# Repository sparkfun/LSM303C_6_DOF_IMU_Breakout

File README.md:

SparkFun LSM303C 6 DOF IMU Breakout
========================================

*[SparkFun LSM303C 6 DOF IMU Breakout (BOB-13303)](https://www.sparkfun.com/products/13303)*

The LSM303C is a triple axis accelerometer and triple axis magnetic sensor, providing 6D of orientation detection.

This part was created in Eagle v7.4.0

Repository Contents
-------------------

* **/Hardware** - All Eagle design files (.brd, .sch)
* **/Libraries** - All Arduino libraries and board examples
* **/Production** - Test bed files and production panel files

Documentation
--------------
* **[Arduino Library](https://github.com/sparkfun/SparkFun_LSM303C_6_DOF_IMU_Breakout_Arduino_Library)** - Arduino library for the LSM303C.
* **[Hookup Guide](https://learn.sparkfun.com/tutorials/lsm303c-6dof-hookup-guide)** - Basic hookup guide for the LSM303C.
* **[SparkFun Fritzing repo](https://github.com/sparkfun/Fritzing_Parts)** - Fritzing diagrams for SparkFun products.
* **[SparkFun 3D Model repo](https://github.com/sparkfun/3D_Models)** - 3D models of SparkFun products. 
* **[SparkFun Graphical Datasheets](https://github.com/sparkfun/Graphical_Datasheets)** -Graphical Datasheets for various SparkFun products

Product Versions
----------------
* [BOB-13303](https://www.sparkfun.com/products/13303)- LSM303C based 6 DOF IMU beakout board

Version History
---------------
* [v1.0_H1.0](https://github.com/sparkfun/LSM303C_6_DOF_IMU_Breakout/releases/tag/v1.0_H1.0) - Removing old libraries. Adding links to formal libs in readme.
* [v1.0](https://github.com/sparkfun/LSM303C_6_DOF_IMU_Breakout/releases/tag/v1.0) - First (hopefully ony) product release.  v10 is SFE code for version 1.0

License Information
-------------------

This product is _**open source**_! 

Please review the LICENSE.md file for license information. 

If you have any questions or concerns on licensing, please contact techsupport@sparkfun.com.

Distributed as-is; no warranty is given.

- Your friends at SparkFun.

_<COLLABORATION CREDIT>_

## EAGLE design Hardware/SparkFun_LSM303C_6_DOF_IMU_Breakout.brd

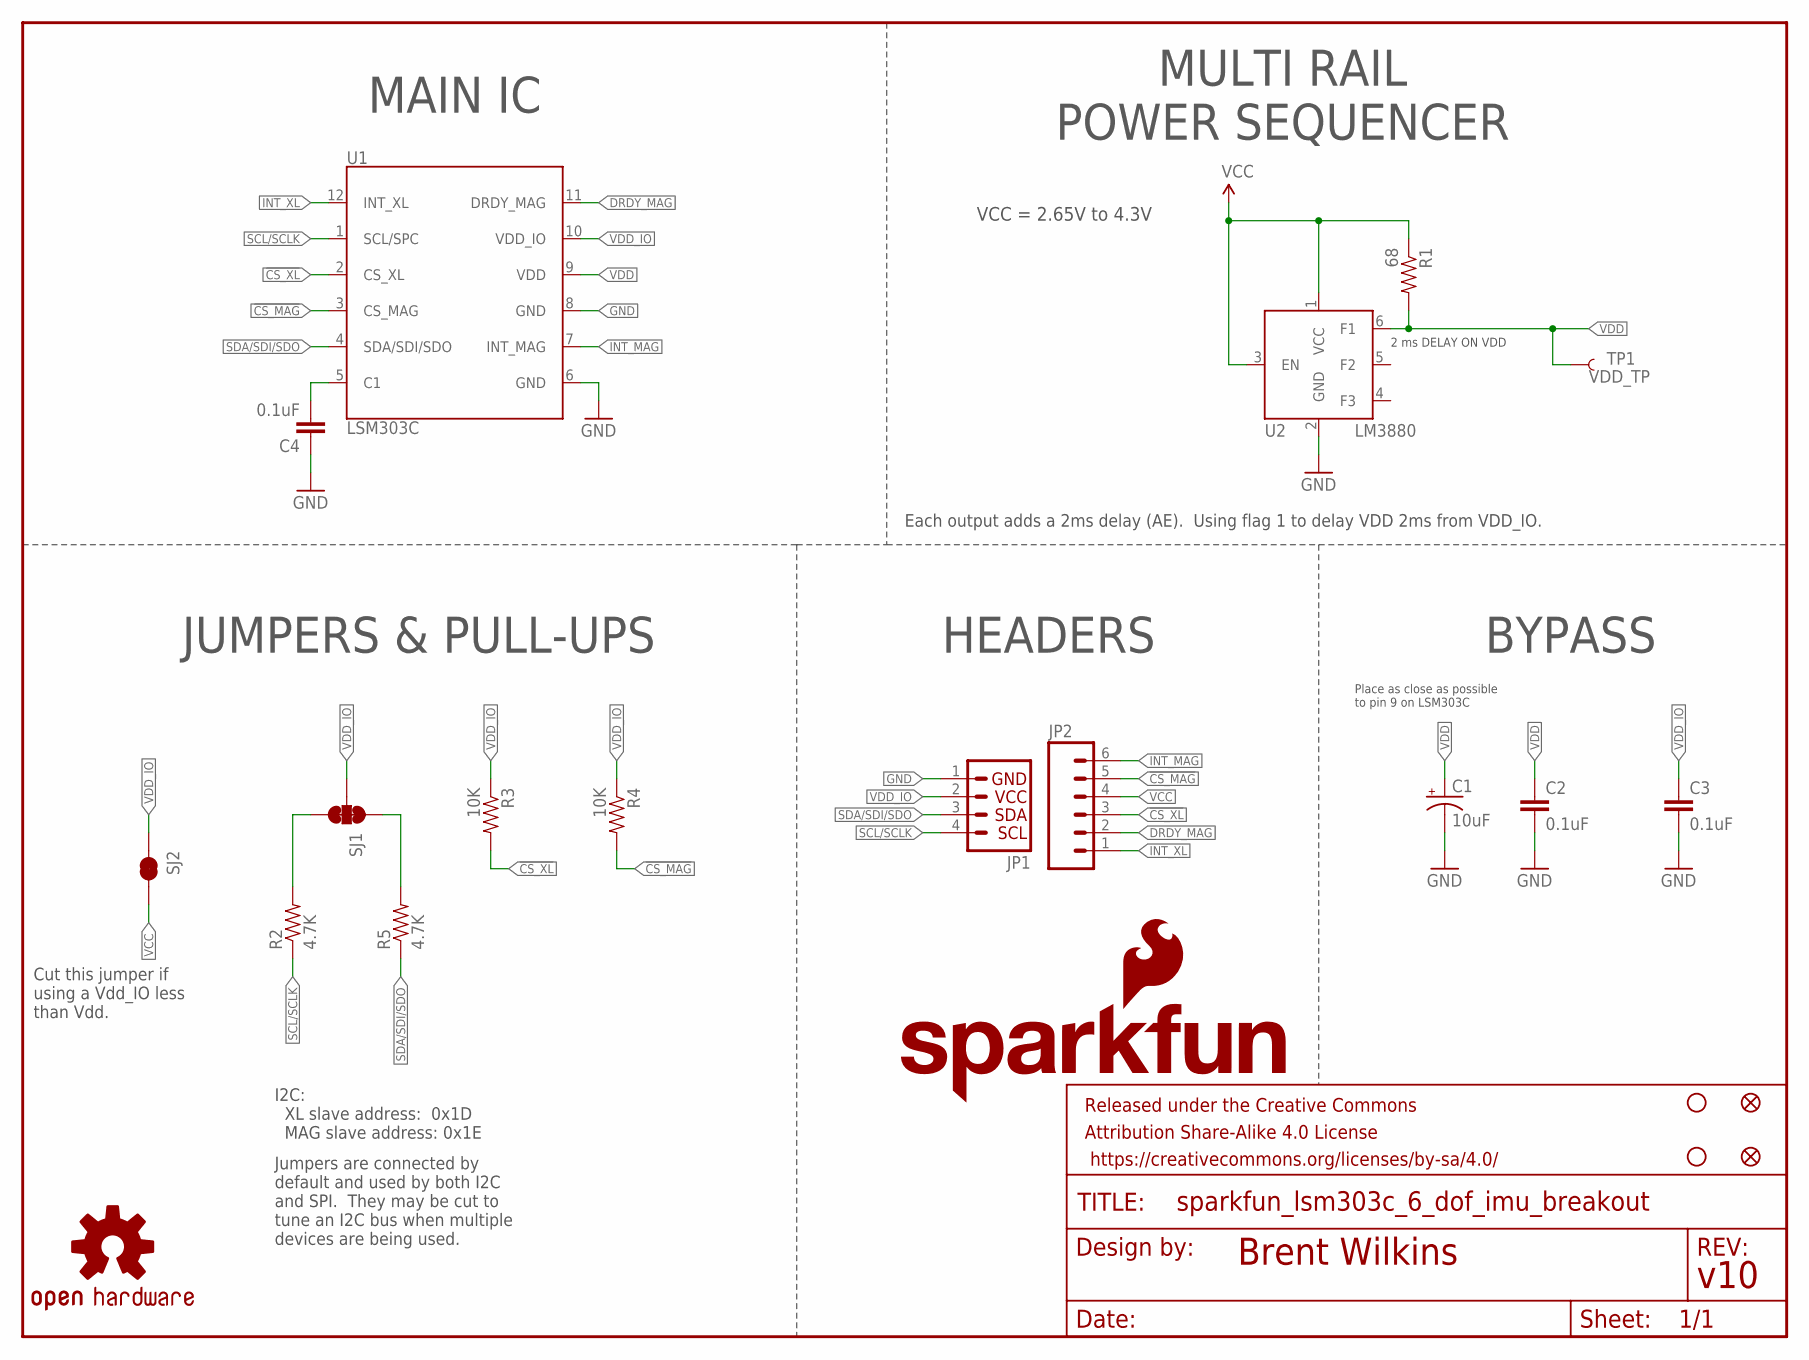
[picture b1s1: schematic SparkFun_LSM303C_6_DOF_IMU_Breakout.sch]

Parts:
C1: 10uF; EIA3216
C2, C3, C4: 0.1uF; 0603-CAP
FID1, FID2: FIDUCIAL1X2; FIDUCIAL-1X2
FRAME1: FRAME-LETTER; CREATIVE_COMMONS
JP1: I2C_STANDARD; 1X04
JP2: M06SILK_FEMALE_PTH; 1X06
LOGO1: SFE_LOGO_NAME.1_INCH; SFE_LOGO_NAME_.1
LOGO2: SFE_LOGO_FLAME.1EXP; SFE_LOGO_FLAME_COPPER_EXPOSED_.1
R1: 68; 0603-RES
R2, R5: 4.7K; 0603-RES
R3, R4: 10K; 0603-RES
SJ1: JUMPER-PAD-3-NC_BY_TRACE; PAD-JUMPER-3-3OF3_NC_BY_TRACE_YES_SILK_FULL_BOX
SJ2: JUMPER-PAD-2-NC_BY_TRACE; PAD-JUMPER-2-NC_BY_TRACE_YES_SILK
STANDOFF1, STANDOFF2: STAND-OFF
TP1: VDD_TP; TP_15TH
U1: LSM303C; LGA-12
U2: LM3880; SOT23-6
U$8: OSHW-LOGOS; OSHW-LOGO-S

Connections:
!CS_MAG: JP2.5, R4.2, U1.3 (CS_MAG)
!CS_XL: JP2.3, R3.2, U1.2 (CS_XL)
DRDY_MAG: JP2.2, U1.11 (DRDY_MAG)
GND: C1.C (-), C2.2, C3.2, C4.1, JP1.1, U1.6 (GND), U1.8 (GND), U2.2 (GND)
I2C-UP: R5.2, SJ1.1
INT_MAG: JP2.6, U1.7 (INT_MAG)
INT_XL: JP2.1, U1.12 (INT_XL)
unnamed: C4.2, U1.5 (C1)
unnamed: R2.2, SJ1.3
SCL/SCLK: JP1.4, R2.1, U1.1 (SCL/SPC)
SDA/SDI/SDO: JP1.3, R5.1, U1.4 (SDA/SDI/SDO)
VCC: JP2.4, R1.1, SJ2.2, U2.1 (VCC), U2.3 (EN)
VDD: C1.A (+), C2.1, R1.2, TP1.P$1, U1.9 (VDD), U2.6 (F1)
VDD_IO: C3.1, JP1.2, R3.1, R4.1, SJ1.2, SJ2.1, U1.10 (VDD_IO)

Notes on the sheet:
2 ms DELAY ON VDD
Place as close as possible to pin 9 on LSM303C
I2C: XL slave address: 0x1D MAG slave address: 0x1E
JUMPERS & PULL-UPS
HEADERS
BYPASS
MULTI RAIL POWER SEQUENCER
MAIN IC
Each output adds a 2ms delay (AE). Using flag 1 to delay VDD 2ms from VDD_IO.
Cut this jumper if using a Vdd_IO less than Vdd.
Jumpers are connected by default and used by both I2C and SPI. They may be cut to tune an I2C bus when multiple devices are being used.
VCC = 2.65V to 4.3V

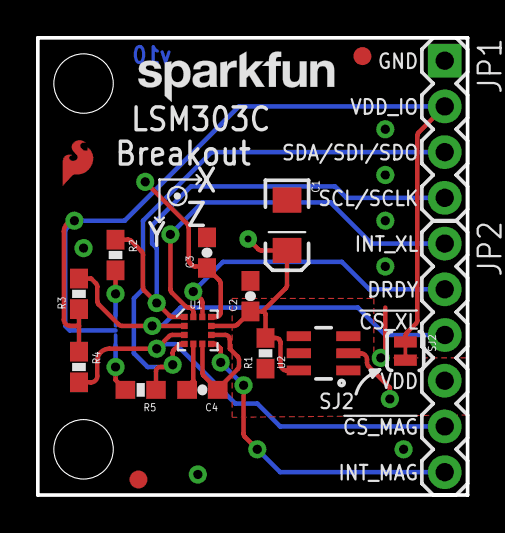
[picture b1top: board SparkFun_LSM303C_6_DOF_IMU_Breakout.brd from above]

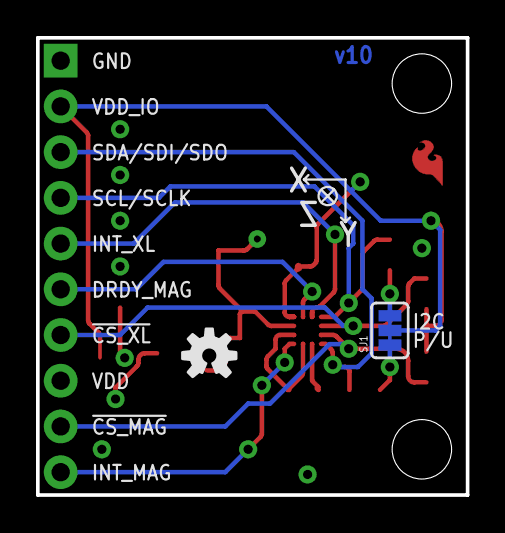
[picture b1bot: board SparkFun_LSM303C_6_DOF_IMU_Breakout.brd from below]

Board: 2 copper layers, 23.9 x 25.4 mm, 24 parts (2 on the bottom side), 14 nets.

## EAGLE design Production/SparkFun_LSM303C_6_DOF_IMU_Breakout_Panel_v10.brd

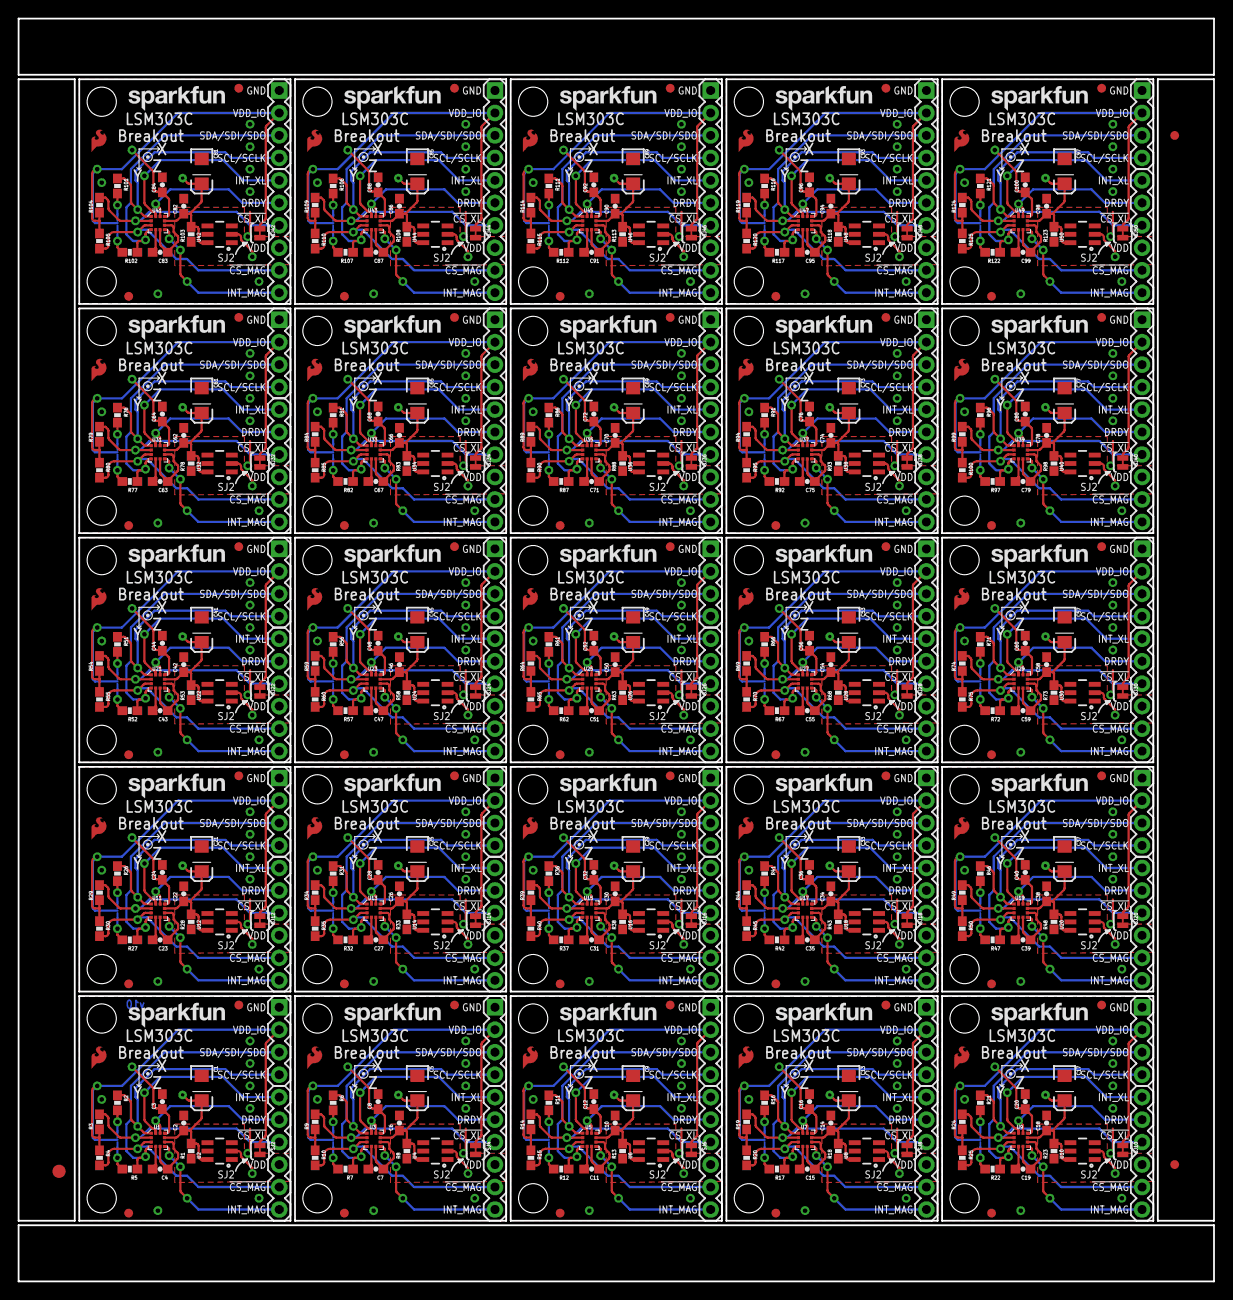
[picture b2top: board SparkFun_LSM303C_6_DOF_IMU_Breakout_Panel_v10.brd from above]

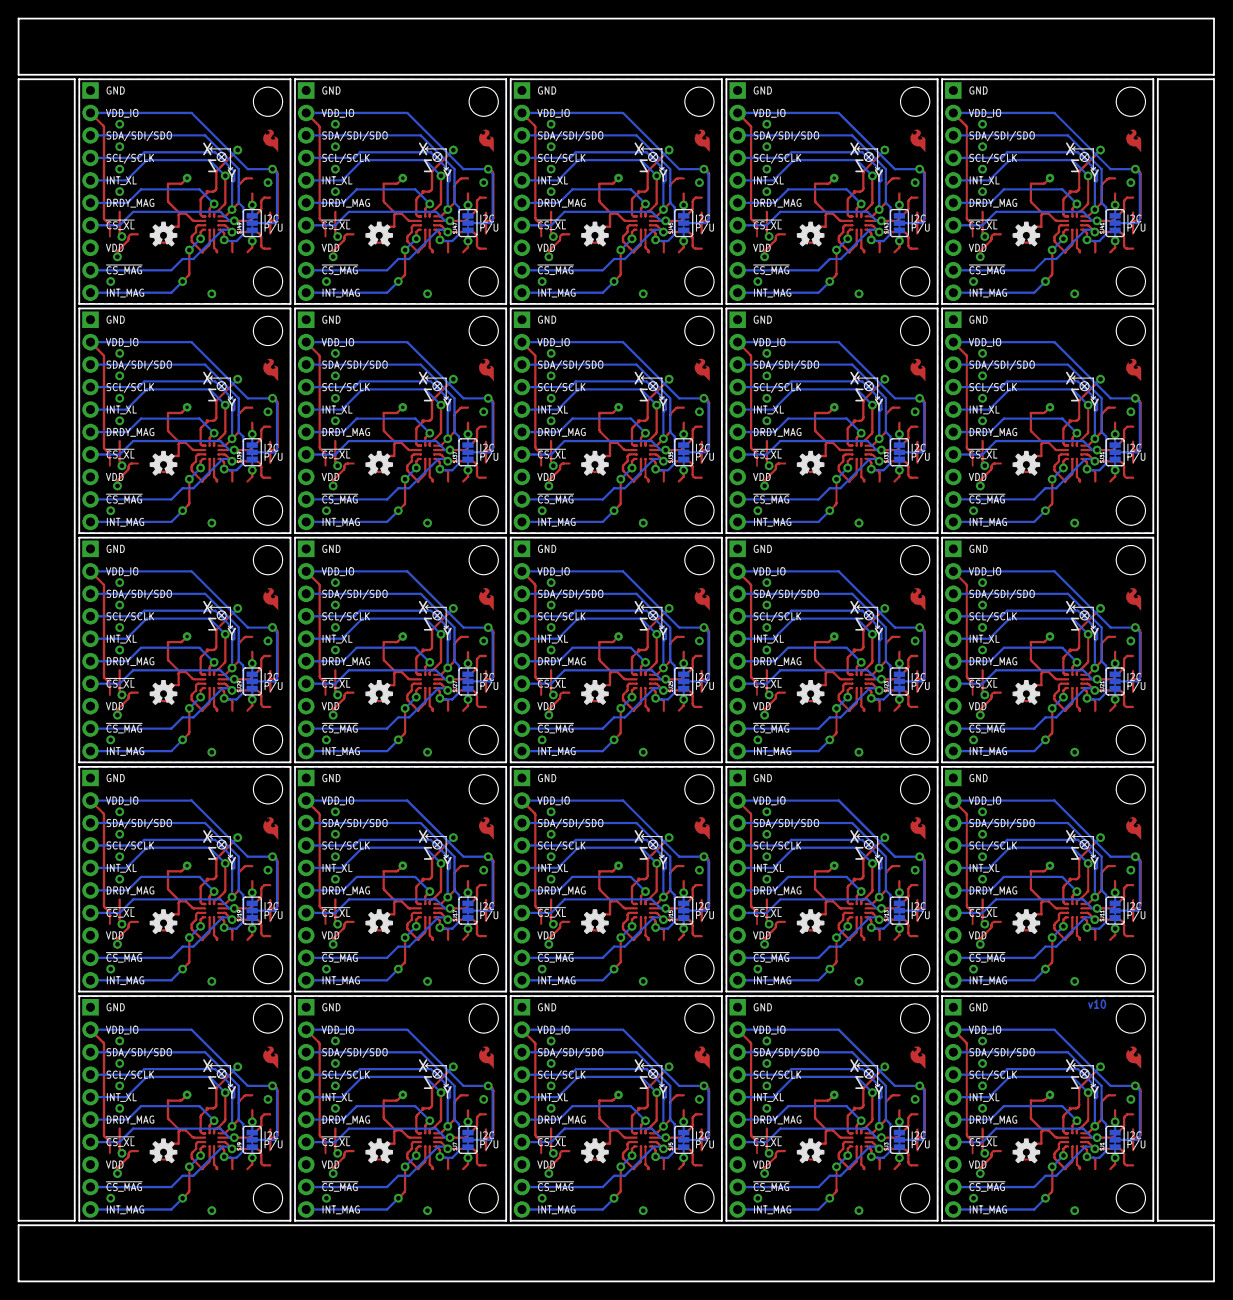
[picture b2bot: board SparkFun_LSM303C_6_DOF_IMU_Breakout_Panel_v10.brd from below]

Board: 2 copper layers, 135.1 x 142.7 mm, 578 parts (50 on the bottom side), 350 nets.

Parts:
C1, C5, C9, C13, C17, C21, C25, C29, C33, C37, C41, C45, C49, C53, C57, C61, C65, C69, C73, C77, C81, C85, C89, C93, C97: 10uF; EIA3216
C2, C3, C4, C6, C7, C8, C10, C11, C12, C14, C15, C16, C18, C19, C20, C22, C23, C24, C26, C27, C28, C30, C31, C32, C34, C35, C36, C38, C39, C40, C42, C43, C44, C46, C47, C48, C50, C51, C52, C54, C55, C56, C58, C59, C60, C62, C63, C64, C66, C67, C68, C70, C71, C72, C74, C75, C76, C78, C79, C80, C82, C83, C84, C86, C87, C88, C90, C91, C92, C94, C95, C96, C98, C99, C100: 0.1uF; 0603-CAP
E$1: FIDUCIAL-1.5X3
E$4, E$5: FIDUCIAL-1X2
FID1, FID2, FID3, FID4, FID5, FID6, FID7, FID8, FID9, FID10, FID11, FID12, FID13, FID14, FID15, FID16, FID17, FID18, FID19, FID20, FID21, FID22, FID23, FID24, FID25, FID26, FID27, FID28, FID29, FID30, FID31, FID32, FID33, FID34, FID35, FID36, FID37, FID38, FID39, FID40, FID41, FID42, FID43, FID44, FID45, FID46, FID47, FID48, FID49, FID50: FIDUCIAL1X2; FIDUCIAL-1X2
JP1, JP4, JP6, JP8, JP10, JP12, JP14, JP16, JP18, JP20, JP22, JP24, JP26, JP28, JP30, JP32, JP34, JP36, JP38, JP40, JP42, JP44, JP46, JP48, JP50: 1X04
JP2, JP3, JP5, JP7, JP9, JP11, JP13, JP15, JP17, JP19, JP21, JP23, JP25, JP27, JP29, JP31, JP33, JP35, JP37, JP39, JP41, JP43, JP45, JP47, JP49: 1X06
LOGO1, LOGO3, LOGO5, LOGO7, LOGO9, LOGO11, LOGO13, LOGO15, LOGO17, LOGO19, LOGO21, LOGO23, LOGO25, LOGO27, LOGO29, LOGO31, LOGO33, LOGO35, LOGO37, LOGO39, LOGO41, LOGO43, LOGO45, LOGO47, LOGO49: SFE_LOGO_NAME.1_INCH; SFE_LOGO_NAME_.1
LOGO2, LOGO4, LOGO6, LOGO8, LOGO10, LOGO12, LOGO14, LOGO16, LOGO18, LOGO20, LOGO22, LOGO24, LOGO26, LOGO28, LOGO30, LOGO32, LOGO34, LOGO36, LOGO38, LOGO40, LOGO42, LOGO44, LOGO46, LOGO48, LOGO50: SFE_LOGO_FLAME.1EXP; SFE_LOGO_FLAME_COPPER_EXPOSED_.1
R1, R8, R13, R18, R23, R28, R33, R38, R43, R48, R53, R58, R63, R68, R73, R78, R83, R88, R93, R98, R103, R108, R113, R118, R123: 68; 0603-RES
R2, R5, R6, R7, R11, R12, R16, R17, R21, R22, R26, R27, R31, R32, R36, R37, R41, R42, R46, R47, R51, R52, R56, R57, R61, R62, R66, R67, R71, R72, R76, R77, R81, R82, R86, R87, R91, R92, R96, R97, R101, R102, R106, R107, R111, R112, R116, R117, R121, R122: 4.7K; 0603-RES
R3, R4, R9, R10, R14, R15, R19, R20, R24, R25, R29, R30, R34, R35, R39, R40, R44, R45, R49, R50, R54, R55, R59, R60, R64, R65, R69, R70, R74, R75, R79, R80, R84, R85, R89, R90, R94, R95, R99, R100, R104, R105, R109, R110, R114, R115, R119, R120, R124, R125: 10K; 0603-RES
SJ1, SJ3, SJ5, SJ7, SJ9, SJ11, SJ13, SJ15, SJ17, SJ19, SJ21, SJ23, SJ25, SJ27, SJ29, SJ31, SJ33, SJ35, SJ37, SJ39, SJ41, SJ43, SJ45, SJ47, SJ49: PAD-JUMPER-3-3OF3_NC_BY_TRACE_YES_SILK_FULL_BOX
SJ2, SJ4, SJ6, SJ8, SJ10, SJ12, SJ14, SJ16, SJ18, SJ20, SJ22, SJ24, SJ26, SJ28, SJ30, SJ32, SJ34, SJ36, SJ38, SJ40, SJ42, SJ44, SJ46, SJ48, SJ50: JUMPER-PAD-2-NC_BY_TRACE; PAD-JUMPER-2-NC_BY_TRACE_YES_SILK
STANDOFF1, STANDOFF2, STANDOFF3, STANDOFF4, STANDOFF5, STANDOFF6, STANDOFF7, STANDOFF8, STANDOFF9, STANDOFF10, STANDOFF11, STANDOFF12, STANDOFF13, STANDOFF14, STANDOFF15, STANDOFF16, STANDOFF17, STANDOFF18, STANDOFF19, STANDOFF20, STANDOFF21, STANDOFF22, STANDOFF23, STANDOFF24, STANDOFF25, STANDOFF26, STANDOFF27, STANDOFF28, STANDOFF29, STANDOFF30, STANDOFF31, STANDOFF32, STANDOFF33, STANDOFF34, STANDOFF35, STANDOFF36, STANDOFF37, STANDOFF38, STANDOFF39, STANDOFF40, STANDOFF41, STANDOFF42, STANDOFF43, STANDOFF44, STANDOFF45, STANDOFF46, STANDOFF47, STANDOFF48, STANDOFF49, STANDOFF50: STAND-OFF
TP1, TP2, TP3, TP4, TP5, TP6, TP7, TP8, TP9, TP10, TP11, TP12, TP13, TP14, TP15, TP16, TP17, TP18, TP19, TP20, TP21, TP22, TP23, TP24, TP25: VDD_TP; TP_15TH
U1, U3, U5, U7, U9, U11, U13, U15, U17, U19, U21, U23, U25, U27, U29, U31, U33, U35, U37, U39, U41, U43, U45, U47, U49: LSM303C; LGA-12
U2, U4, U6, U8, U10, U12, U14, U16, U18, U20, U22, U24, U26, U28, U30, U32, U34, U36, U38, U40, U42, U44, U46, U48, U50: LM3880; SOT23-6
U$1, U$2, U$3, U$4, U$5, U$6, U$7, U$8, U$9, U$10, U$11, U$12, U$13, U$14, U$15, U$16, U$17, U$18, U$19, U$20, U$21, U$22, U$23, U$24, U$25: OSHW-LOGOS; OSHW-LOGO-S

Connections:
!CS_MAG: JP2.5, R4.2, U1.3
!CS_MAG1: JP3.5, R10.2, U3.3
!CS_MAG2: JP5.5, R15.2, U5.3
!CS_MAG3: JP7.5, R20.2, U7.3
!CS_MAG4: JP9.5, R25.2, U9.3
!CS_MAG5: JP11.5, R30.2, U11.3
!CS_MAG6: JP13.5, R35.2, U13.3
!CS_MAG7: JP15.5, R40.2, U15.3
!CS_MAG8: JP17.5, R45.2, U17.3
!CS_MAG9: JP19.5, R50.2, U19.3
!CS_MAG10: JP21.5, R55.2, U21.3
!CS_MAG11: JP23.5, R60.2, U23.3
!CS_MAG12: JP25.5, R65.2, U25.3
!CS_MAG13: JP27.5, R70.2, U27.3
!CS_MAG14: JP29.5, R75.2, U29.3
!CS_MAG15: JP31.5, R80.2, U31.3
!CS_MAG16: JP33.5, R85.2, U33.3
!CS_MAG17: JP35.5, R90.2, U35.3
!CS_MAG18: JP37.5, R95.2, U37.3
!CS_MAG19: JP39.5, R100.2, U39.3
!CS_MAG20: JP41.5, R105.2, U41.3
!CS_MAG21: JP43.5, R110.2, U43.3
!CS_MAG22: JP45.5, R115.2, U45.3
!CS_MAG23: JP47.5, R120.2, U47.3
!CS_MAG24: JP49.5, R125.2, U49.3
!CS_XL: JP2.3, R3.2, U1.2
!CS_XL1: JP3.3, R9.2, U3.2
!CS_XL2: JP5.3, R14.2, U5.2
!CS_XL3: JP7.3, R19.2, U7.2
!CS_XL4: JP9.3, R24.2, U9.2
!CS_XL5: JP11.3, R29.2, U11.2
!CS_XL6: JP13.3, R34.2, U13.2
!CS_XL7: JP15.3, R39.2, U15.2
!CS_XL8: JP17.3, R44.2, U17.2
!CS_XL9: JP19.3, R49.2, U19.2
!CS_XL10: JP21.3, R54.2, U21.2
!CS_XL11: JP23.3, R59.2, U23.2
!CS_XL12: JP25.3, R64.2, U25.2
!CS_XL13: JP27.3, R69.2, U27.2
!CS_XL14: JP29.3, R74.2, U29.2
!CS_XL15: JP31.3, R79.2, U31.2
!CS_XL16: JP33.3, R84.2, U33.2
!CS_XL17: JP35.3, R89.2, U35.2
!CS_XL18: JP37.3, R94.2, U37.2
!CS_XL19: JP39.3, R99.2, U39.2
!CS_XL20: JP41.3, R104.2, U41.2
!CS_XL21: JP43.3, R109.2, U43.2
!CS_XL22: JP45.3, R114.2, U45.2
!CS_XL23: JP47.3, R119.2, U47.2
!CS_XL24: JP49.3, R124.2, U49.2
DRDY_MAG: JP2.2, U1.11
DRDY_MAG1: JP3.2, U3.11
DRDY_MAG2: JP5.2, U5.11
DRDY_MAG3: JP7.2, U7.11
DRDY_MAG4: JP9.2, U9.11
DRDY_MAG5: JP11.2, U11.11
DRDY_MAG6: JP13.2, U13.11
DRDY_MAG7: JP15.2, U15.11
DRDY_MAG8: JP17.2, U17.11
DRDY_MAG9: JP19.2, U19.11
DRDY_MAG10: JP21.2, U21.11
DRDY_MAG11: JP23.2, U23.11
DRDY_MAG12: JP25.2, U25.11
DRDY_MAG13: JP27.2, U27.11
DRDY_MAG14: JP29.2, U29.11
DRDY_MAG15: JP31.2, U31.11
DRDY_MAG16: JP33.2, U33.11
DRDY_MAG17: JP35.2, U35.11
DRDY_MAG18: JP37.2, U37.11
DRDY_MAG19: JP39.2, U39.11
DRDY_MAG20: JP41.2, U41.11
DRDY_MAG21: JP43.2, U43.11
DRDY_MAG22: JP45.2, U45.11
DRDY_MAG23: JP47.2, U47.11
DRDY_MAG24: JP49.2, U49.11
GND: C1.C, C2.2, C3.2, C4.1, JP1.1, U1.6, U1.8, U2.2
GND1: C5.C, C6.2, C7.1, C8.2, JP4.1, U3.6, U3.8, U4.2
GND2: C9.C, C10.2, C11.1, C12.2, JP6.1, U5.6, U5.8, U6.2
GND3: C13.C, C14.2, C15.1, C16.2, JP8.1, U7.6, U7.8, U8.2
GND4: C17.C, C18.2, C19.1, C20.2, JP10.1, U9.6, U9.8, U10.2
GND5: C21.C, C22.2, C23.1, C24.2, JP12.1, U11.6, U11.8, U12.2
GND6: C25.C, C26.2, C27.1, C28.2, JP14.1, U13.6, U13.8, U14.2
GND7: C29.C, C30.2, C31.1, C32.2, JP16.1, U15.6, U15.8, U16.2
GND8: C33.C, C34.2, C35.1, C36.2, JP18.1, U17.6, U17.8, U18.2
GND9: C37.C, C38.2, C39.1, C40.2, JP20.1, U19.6, U19.8, U20.2
GND10: C41.C, C42.2, C43.1, C44.2, JP22.1, U21.6, U21.8, U22.2
GND11: C45.C, C46.2, C47.1, C48.2, JP24.1, U23.6, U23.8, U24.2
GND12: C49.C, C50.2, C51.1, C52.2, JP26.1, U25.6, U25.8, U26.2
GND13: C53.C, C54.2, C55.1, C56.2, JP28.1, U27.6, U27.8, U28.2
GND14: C57.C, C58.2, C59.1, C60.2, JP30.1, U29.6, U29.8, U30.2
GND15: C61.C, C62.2, C63.1, C64.2, JP32.1, U31.6, U31.8, U32.2
GND16: C65.C, C66.2, C67.1, C68.2, JP34.1, U33.6, U33.8, U34.2
GND17: C69.C, C70.2, C71.1, C72.2, JP36.1, U35.6, U35.8, U36.2
GND18: C73.C, C74.2, C75.1, C76.2, JP38.1, U37.6, U37.8, U38.2
GND19: C77.C, C78.2, C79.1, C80.2, JP40.1, U39.6, U39.8, U40.2
GND20: C81.C, C82.2, C83.1, C84.2, JP42.1, U41.6, U41.8, U42.2
GND21: C85.C, C86.2, C87.1, C88.2, JP44.1, U43.6, U43.8, U44.2
GND22: C89.C, C90.2, C91.1, C92.2, JP46.1, U45.6, U45.8, U46.2
GND23: C93.C, C94.2, C95.1, C96.2, JP48.1, U47.6, U47.8, U48.2
GND24: C97.C, C98.2, C99.1, C100.2, JP50.1, U49.6, U49.8, U50.2
I2C-UP: R5.2, SJ1.1
I2C-UP1: R7.2, SJ3.1
I2C-UP2: R12.2, SJ5.1
I2C-UP3: R17.2, SJ7.1
I2C-UP4: R22.2, SJ9.1
I2C-UP5: R27.2, SJ11.1
I2C-UP6: R32.2, SJ13.1
I2C-UP7: R37.2, SJ15.1
I2C-UP8: R42.2, SJ17.1
I2C-UP9: R47.2, SJ19.1
I2C-UP10: R52.2, SJ21.1
I2C-UP11: R57.2, SJ23.1
I2C-UP12: R62.2, SJ25.1
I2C-UP13: R67.2, SJ27.1
I2C-UP14: R72.2, SJ29.1
I2C-UP15: R77.2, SJ31.1
I2C-UP16: R82.2, SJ33.1
I2C-UP17: R87.2, SJ35.1
I2C-UP18: R92.2, SJ37.1
I2C-UP19: R97.2, SJ39.1
I2C-UP20: R102.2, SJ41.1
I2C-UP21: R107.2, SJ43.1
I2C-UP22: R112.2, SJ45.1
I2C-UP23: R117.2, SJ47.1
I2C-UP24: R122.2, SJ49.1
INT_MAG: JP2.6, U1.7
INT_MAG1: JP3.6, U3.7
INT_MAG2: JP5.6, U5.7
INT_MAG3: JP7.6, U7.7
INT_MAG4: JP9.6, U9.7
INT_MAG5: JP11.6, U11.7
INT_MAG6: JP13.6, U13.7
INT_MAG7: JP15.6, U15.7
INT_MAG8: JP17.6, U17.7
INT_MAG9: JP19.6, U19.7
INT_MAG10: JP21.6, U21.7
INT_MAG11: JP23.6, U23.7
INT_MAG12: JP25.6, U25.7
INT_MAG13: JP27.6, U27.7
INT_MAG14: JP29.6, U29.7
INT_MAG15: JP31.6, U31.7
INT_MAG16: JP33.6, U33.7
INT_MAG17: JP35.6, U35.7
INT_MAG18: JP37.6, U37.7
INT_MAG19: JP39.6, U39.7
INT_MAG20: JP41.6, U41.7
INT_MAG21: JP43.6, U43.7
INT_MAG22: JP45.6, U45.7
INT_MAG23: JP47.6, U47.7
INT_MAG24: JP49.6, U49.7
INT_XL: JP2.1, U1.12
INT_XL1: JP3.1, U3.12
INT_XL2: JP5.1, U5.12
INT_XL3: JP7.1, U7.12
INT_XL4: JP9.1, U9.12
INT_XL5: JP11.1, U11.12
INT_XL6: JP13.1, U13.12
INT_XL7: JP15.1, U15.12
INT_XL8: JP17.1, U17.12
INT_XL9: JP19.1, U19.12
INT_XL10: JP21.1, U21.12
INT_XL11: JP23.1, U23.12
INT_XL12: JP25.1, U25.12
INT_XL13: JP27.1, U27.12
INT_XL14: JP29.1, U29.12
INT_XL15: JP31.1, U31.12
INT_XL16: JP33.1, U33.12
INT_XL17: JP35.1, U35.12
INT_XL18: JP37.1, U37.12
INT_XL19: JP39.1, U39.12
INT_XL20: JP41.1, U41.12
INT_XL21: JP43.1, U43.12
INT_XL22: JP45.1, U45.12
INT_XL23: JP47.1, U47.12
INT_XL24: JP49.1, U49.12
unnamed: C4.2, U1.5
unnamed: R2.2, SJ1.3
unnamed: C7.2, U3.5
unnamed: R6.2, SJ3.3
unnamed: C11.2, U5.5
unnamed: R11.2, SJ5.3
unnamed: C15.2, U7.5
unnamed: R16.2, SJ7.3
unnamed: C19.2, U9.5
unnamed: R21.2, SJ9.3
unnamed: C23.2, U11.5
unnamed: R26.2, SJ11.3
unnamed: C27.2, U13.5
unnamed: R31.2, SJ13.3
unnamed: C31.2, U15.5
unnamed: R36.2, SJ15.3
unnamed: C35.2, U17.5
unnamed: R41.2, SJ17.3
unnamed: C39.2, U19.5
unnamed: R46.2, SJ19.3
unnamed: C43.2, U21.5
unnamed: R51.2, SJ21.3
unnamed: C47.2, U23.5
unnamed: R56.2, SJ23.3
unnamed: C51.2, U25.5
unnamed: R61.2, SJ25.3
unnamed: C55.2, U27.5
unnamed: R66.2, SJ27.3
unnamed: C59.2, U29.5
unnamed: R71.2, SJ29.3
unnamed: C63.2, U31.5
unnamed: R76.2, SJ31.3
unnamed: C67.2, U33.5
unnamed: R81.2, SJ33.3
unnamed: C71.2, U35.5
unnamed: R86.2, SJ35.3
unnamed: C75.2, U37.5
unnamed: R91.2, SJ37.3
unnamed: C79.2, U39.5
unnamed: R96.2, SJ39.3
unnamed: C83.2, U41.5
unnamed: R101.2, SJ41.3
unnamed: C87.2, U43.5
unnamed: R106.2, SJ43.3
unnamed: C91.2, U45.5
unnamed: R111.2, SJ45.3
unnamed: C95.2, U47.5
unnamed: R116.2, SJ47.3
unnamed: C99.2, U49.5
unnamed: R121.2, SJ49.3
SCL/SCLK: JP1.4, R2.1, U1.1
SCL/SCLK1: JP4.4, R6.1, U3.1
SCL/SCLK2: JP6.4, R11.1, U5.1
SCL/SCLK3: JP8.4, R16.1, U7.1
SCL/SCLK4: JP10.4, R21.1, U9.1
SCL/SCLK5: JP12.4, R26.1, U11.1
SCL/SCLK6: JP14.4, R31.1, U13.1
SCL/SCLK7: JP16.4, R36.1, U15.1
SCL/SCLK8: JP18.4, R41.1, U17.1
SCL/SCLK9: JP20.4, R46.1, U19.1
SCL/SCLK10: JP22.4, R51.1, U21.1
SCL/SCLK11: JP24.4, R56.1, U23.1
SCL/SCLK12: JP26.4, R61.1, U25.1
SCL/SCLK13: JP28.4, R66.1, U27.1
SCL/SCLK14: JP30.4, R71.1, U29.1
SCL/SCLK15: JP32.4, R76.1, U31.1
SCL/SCLK16: JP34.4, R81.1, U33.1
SCL/SCLK17: JP36.4, R86.1, U35.1
SCL/SCLK18: JP38.4, R91.1, U37.1
SCL/SCLK19: JP40.4, R96.1, U39.1
SCL/SCLK20: JP42.4, R101.1, U41.1
SCL/SCLK21: JP44.4, R106.1, U43.1
SCL/SCLK22: JP46.4, R111.1, U45.1
SCL/SCLK23: JP48.4, R116.1, U47.1
SCL/SCLK24: JP50.4, R121.1, U49.1
SDA/SDI/SDO: JP1.3, R5.1, U1.4
SDA/SDI/SDO1: JP4.3, R7.1, U3.4
SDA/SDI/SDO2: JP6.3, R12.1, U5.4
SDA/SDI/SDO3: JP8.3, R17.1, U7.4
SDA/SDI/SDO4: JP10.3, R22.1, U9.4
SDA/SDI/SDO5: JP12.3, R27.1, U11.4
SDA/SDI/SDO6: JP14.3, R32.1, U13.4
SDA/SDI/SDO7: JP16.3, R37.1, U15.4
SDA/SDI/SDO8: JP18.3, R42.1, U17.4
SDA/SDI/SDO9: JP20.3, R47.1, U19.4
SDA/SDI/SDO10: JP22.3, R52.1, U21.4
SDA/SDI/SDO11: JP24.3, R57.1, U23.4
SDA/SDI/SDO12: JP26.3, R62.1, U25.4
SDA/SDI/SDO13: JP28.3, R67.1, U27.4
SDA/SDI/SDO14: JP30.3, R72.1, U29.4
SDA/SDI/SDO15: JP32.3, R77.1, U31.4
SDA/SDI/SDO16: JP34.3, R82.1, U33.4
SDA/SDI/SDO17: JP36.3, R87.1, U35.4
SDA/SDI/SDO18: JP38.3, R92.1, U37.4
SDA/SDI/SDO19: JP40.3, R97.1, U39.4
SDA/SDI/SDO20: JP42.3, R102.1, U41.4
SDA/SDI/SDO21: JP44.3, R107.1, U43.4
SDA/SDI/SDO22: JP46.3, R112.1, U45.4
SDA/SDI/SDO23: JP48.3, R117.1, U47.4
SDA/SDI/SDO24: JP50.3, R122.1, U49.4
VCC: JP2.4, R1.1, SJ2.2, U2.1, U2.3
VCC1: JP3.4, R8.1, SJ4.2, U4.1, U4.3
VCC2: JP5.4, R13.1, SJ6.2, U6.1, U6.3
VCC3: JP7.4, R18.1, SJ8.2, U8.1, U8.3
VCC4: JP9.4, R23.1, SJ10.2, U10.1, U10.3
VCC5: JP11.4, R28.1, SJ12.2, U12.1, U12.3
VCC6: JP13.4, R33.1, SJ14.2, U14.1, U14.3
VCC7: JP15.4, R38.1, SJ16.2, U16.1, U16.3
VCC8: JP17.4, R43.1, SJ18.2, U18.1, U18.3
VCC9: JP19.4, R48.1, SJ20.2, U20.1, U20.3
VCC10: JP21.4, R53.1, SJ22.2, U22.1, U22.3
VCC11: JP23.4, R58.1, SJ24.2, U24.1, U24.3
VCC12: JP25.4, R63.1, SJ26.2, U26.1, U26.3
VCC13: JP27.4, R68.1, SJ28.2, U28.1, U28.3
VCC14: JP29.4, R73.1, SJ30.2, U30.1, U30.3
VCC15: JP31.4, R78.1, SJ32.2, U32.1, U32.3
VCC16: JP33.4, R83.1, SJ34.2, U34.1, U34.3
VCC17: JP35.4, R88.1, SJ36.2, U36.1, U36.3
VCC18: JP37.4, R93.1, SJ38.2, U38.1, U38.3
VCC19: JP39.4, R98.1, SJ40.2, U40.1, U40.3
VCC20: JP41.4, R103.1, SJ42.2, U42.1, U42.3
VCC21: JP43.4, R108.1, SJ44.2, U44.1, U44.3
VCC22: JP45.4, R113.1, SJ46.2, U46.1, U46.3
VCC23: JP47.4, R118.1, SJ48.2, U48.1, U48.3
VCC24: JP49.4, R123.1, SJ50.2, U50.1, U50.3
VDD: C1.A, C2.1, R1.2, TP1.P$1, U1.9, U2.6
VDD1: C5.A, C6.1, R8.2, TP2.P$1, U3.9, U4.6
VDD2: C9.A, C10.1, R13.2, TP3.P$1, U5.9, U6.6
VDD3: C13.A, C14.1, R18.2, TP4.P$1, U7.9, U8.6
VDD4: C17.A, C18.1, R23.2, TP5.P$1, U9.9, U10.6
VDD5: C21.A, C22.1, R28.2, TP6.P$1, U11.9, U12.6
VDD6: C25.A, C26.1, R33.2, TP7.P$1, U13.9, U14.6
VDD7: C29.A, C30.1, R38.2, TP8.P$1, U15.9, U16.6
VDD8: C33.A, C34.1, R43.2, TP9.P$1, U17.9, U18.6
VDD9: C37.A, C38.1, R48.2, TP10.P$1, U19.9, U20.6
VDD10: C41.A, C42.1, R53.2, TP11.P$1, U21.9, U22.6
VDD11: C45.A, C46.1, R58.2, TP12.P$1, U23.9, U24.6
VDD12: C49.A, C50.1, R63.2, TP13.P$1, U25.9, U26.6
VDD13: C53.A, C54.1, R68.2, TP14.P$1, U27.9, U28.6
VDD14: C57.A, C58.1, R73.2, TP15.P$1, U29.9, U30.6
VDD15: C61.A, C62.1, R78.2, TP16.P$1, U31.9, U32.6
VDD16: C65.A, C66.1, R83.2, TP17.P$1, U33.9, U34.6
VDD17: C69.A, C70.1, R88.2, TP18.P$1, U35.9, U36.6
VDD18: C73.A, C74.1, R93.2, TP19.P$1, U37.9, U38.6
VDD19: C77.A, C78.1, R98.2, TP20.P$1, U39.9, U40.6
VDD20: C81.A, C82.1, R103.2, TP21.P$1, U41.9, U42.6
VDD21: C85.A, C86.1, R108.2, TP22.P$1, U43.9, U44.6
VDD22: C89.A, C90.1, R113.2, TP23.P$1, U45.9, U46.6
VDD23: C93.A, C94.1, R118.2, TP24.P$1, U47.9, U48.6
VDD24: C97.A, C98.1, R123.2, TP25.P$1, U49.9, U50.6
VDD_IO: C3.1, JP1.2, R3.1, R4.1, SJ1.2, SJ2.1, U1.10
VDD_IO1: C8.1, JP4.2, R9.1, R10.1, SJ3.2, SJ4.1, U3.10
VDD_IO2: C12.1, JP6.2, R14.1, R15.1, SJ5.2, SJ6.1, U5.10
VDD_IO3: C16.1, JP8.2, R19.1, R20.1, SJ7.2, SJ8.1, U7.10
VDD_IO4: C20.1, JP10.2, R24.1, R25.1, SJ9.2, SJ10.1, U9.10
VDD_IO5: C24.1, JP12.2, R29.1, R30.1, SJ11.2, SJ12.1, U11.10
VDD_IO6: C28.1, JP14.2, R34.1, R35.1, SJ13.2, SJ14.1, U13.10
VDD_IO7: C32.1, JP16.2, R39.1, R40.1, SJ15.2, SJ16.1, U15.10
VDD_IO8: C36.1, JP18.2, R44.1, R45.1, SJ17.2, SJ18.1, U17.10
VDD_IO9: C40.1, JP20.2, R49.1, R50.1, SJ19.2, SJ20.1, U19.10
VDD_IO10: C44.1, JP22.2, R54.1, R55.1, SJ21.2, SJ22.1, U21.10
VDD_IO11: C48.1, JP24.2, R59.1, R60.1, SJ23.2, SJ24.1, U23.10
VDD_IO12: C52.1, JP26.2, R64.1, R65.1, SJ25.2, SJ26.1, U25.10
VDD_IO13: C56.1, JP28.2, R69.1, R70.1, SJ27.2, SJ28.1, U27.10
VDD_IO14: C60.1, JP30.2, R74.1, R75.1, SJ29.2, SJ30.1, U29.10
VDD_IO15: C64.1, JP32.2, R79.1, R80.1, SJ31.2, SJ32.1, U31.10
VDD_IO16: C68.1, JP34.2, R84.1, R85.1, SJ33.2, SJ34.1, U33.10
VDD_IO17: C72.1, JP36.2, R89.1, R90.1, SJ35.2, SJ36.1, U35.10
VDD_IO18: C76.1, JP38.2, R94.1, R95.1, SJ37.2, SJ38.1, U37.10
VDD_IO19: C80.1, JP40.2, R99.1, R100.1, SJ39.2, SJ40.1, U39.10
VDD_IO20: C84.1, JP42.2, R104.1, R105.1, SJ41.2, SJ42.1, U41.10
VDD_IO21: C88.1, JP44.2, R109.1, R110.1, SJ43.2, SJ44.1, U43.10
VDD_IO22: C92.1, JP46.2, R114.1, R115.1, SJ45.2, SJ46.1, U45.10
VDD_IO23: C96.1, JP48.2, R119.1, R120.1, SJ47.2, SJ48.1, U47.10
VDD_IO24: C100.1, JP50.2, R124.1, R125.1, SJ49.2, SJ50.1, U49.10

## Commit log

2015-02-13 Ready for proto review
2015-02-13 Ready for final proto review
2015-02-13 Added dimensions
2015-02-17 Addded another mounting hole, removed documentation, & made I2C by default
2015-02-17 Fixed typo in README
2015-02-17 Changed pullups abbreviation to P/U
2015-02-18 Added PROD-IDs to all placed parts
2015-02-19 Silk work
2015-02-19 Closed VDD-VDD_IO jumper making the PCBA single input volatage (3.3V) by default
2015-05-06 Added .gitattributes
2015-06-01 Fixed logic inversion bug and simplified board by removing jumpers
2015-06-01 Updated SKU of 68Ω resistor
2015-06-02 Small tweaks
2015-06-02 Fixed 'width' dimension
2015-06-02 Moved CS_XL out from under LSM303C
2015-06-02 Moved CS_MAG out from under LSM303C
2015-06-02 Straightened CS_MAG
2015-06-02 Resolved QC issues
2015-06-02 Adjusted trace under pad
2015-08-12 Incremented version number
2015-08-13 Renamed SJ4 & moved a dim to layer 47
2015-08-14 Moved "inches note" to measures layer
    Moved "All units in inches" note from dimension to measures layer.
2015-08-19 created panel v10
2015-09-28 Fixed typo in note
2015-10-06 Squashed 'Libraries/Arduino/' content from commit f84d633
    git-subtree-dir: Libraries/Arduino
    git-subtree-split: f84d633edc27f09ee3d260810be5eb51c1b12e13
2015-10-06 Added subtree & README
2015-10-08 Updated README with pic, etc.
2015-12-22 Squashed 'Libraries/Arduino/' changes from f84d633..da3a509
    da3a509 Updated README with new release
    c6f465a Explicitly set the I2C speed to 400kHz
    git-subtree-dir: Libraries/Arduino
    git-subtree-split: da3a509b6cc8d50fff9ffc4cd9694e2ae8b64de5
2015-12-22 Added subtree command to README & pulled in new Arduino library release
2016-01-21 Added Doc and Updated License
2016-01-21 Added product name to readme doc
2019-05-31 Removing old libraries. Adding links to formal libs in readme.
    - Removing subtree and linking to Arduino library repo to keep up with the latest changes in code.

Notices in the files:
parts and their libraries:
SparkFun-Aesthetics: Licensing: Creative Commons ShareAlike 4.0 International - https://creativecommons.org/licenses/by-sa/4.0
SparkFun-Aesthetics: Released under the Creative Commons Attribution Share-Alike 4.0 License
SparkFun-Aesthetics: https://creativecommons.org/licenses/by-sa/4.0
